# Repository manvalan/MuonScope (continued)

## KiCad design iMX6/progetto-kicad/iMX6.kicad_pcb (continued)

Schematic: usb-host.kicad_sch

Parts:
C212: 1uF; C_0603_1608Metric
C213: 47uF/10V; C_1206_3216Metric
C214: 100nF; C_0603_1608Metric
J9: TYPE-C-31-M-12; USB-C_SMD-TYPE-C-31-M-12_1; MPN TYPE-C-31-M-12; LCSC C165948
J10: Console UART1; PinHeader_1x03_P2.54mm_Vertical; MPN 2.54-1*3P; LCSC C49257
R217, R218: 56k; R_0603_1608Metric
R219: 26.1k 1%; R_0603_1608Metric
R220: 100k; R_0603_1608Metric
R221: 10k; R_0603_1608Metric
U16: TPS2553DBVR; TPS2553DBVR_SOT-23-6_L2.9-W1.6-P0.95-LS2.8-BR; MPN TPS2553DBVR; LCSC C55266
U17: USBLC6-2SC6; SOT-23-6; MPN USBLC6-2SC6; LCSC C7519

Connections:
5V: C212.1, R217.1, R218.1, U16.1 (IN); also elsewhere on the board
/USB host e console/USB2_CC1: J9.A5 (CC1), R217.2
/USB host e console/USB2_CC2: J9.B5 (CC2), R218.2
/USB host e console/USB2_ILIM: R219.1, U16.5 (ILIM)
/USB host e console/VBUS2: C213.1, C214.1, J9.A4B9 (VBUS), J9.B4A9 (VBUS), U16.6 (OUT), U17.5 (VBUS)
DCDC_3V3: R221.1; also elsewhere on the board
GND: C212.2, C213.2, C214.2, J9.1 (EH), J9.2 (EH), J9.3 (EH), J9.4 (EH), J9.A1B12 (GND), J9.B1A12 (GND), J10.3, R219.2, R220.2, U16.2 (GND), U17.2 (GND); also elsewhere on the board
UART1_RX: J10.2; also elsewhere on the board
UART1_TX: J10.1; also elsewhere on the board
USB2_DM: J9.A7 (DN1), J9.B7 (DN2), U17.3 (I/O2), U17.4 (I/O2); also elsewhere on the board
USB2_DP: J9.A6 (DP1), J9.B6 (DP2), U17.1 (I/O1), U17.6 (I/O1); also elsewhere on the board
USB2_OC_N: R221.2, U16.4 (/FAULT); also elsewhere on the board
USB2_VBUS_EN: R220.1, U16.3 (EN); also elsewhere on the board

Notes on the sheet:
USB-C 2 host su USB_OTG2 (ex hub), affiancata alla USB-C 1. VBUS dal TPS2553 (~1 A, RILIM 26.1k), EN su GPIO1_IO04 con 100k a GND, FAULT su SNVS_TAMPER6 con 10k. Rp 56k su CC (sorgente default).
Console Linux su UART1 (al posto del CP2102N di nanoberry): header 1x3 TX, RX, GND a 3.3 V.
USB-C 2 host

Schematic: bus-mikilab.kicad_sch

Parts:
C215: 100nF; C_0603_1608Metric
J11: BUS_POWER_MIKILAB; FPC-SMD_FH12-30S-0.5SH-55; MPN FH12-30S-0.5SH; LCSC C506793
J12: BUS_MIKILAB_MAIN; FPC-SMD_28P-P0.50_FPC-05F-28PH20; MPN FPC-05F-28PH20; LCSC C2856807
R222, R223: 33R; R_0603_1608Metric
R224: 10k; R_0603_1608Metric
R225: 100k; R_0603_1608Metric
R226, R227: 4.7k; R_0603_1608Metric
R228, R229: 2.2k; R_0603_1608Metric
U18, U19, U20, U21, U22, U23: TPD4E05U06DQAR; USON-10_2.5x1.0mm_P0.5mm; MPN TPD4E05U06DQAR

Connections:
/Bus MIKILAB/BUS_1V25_REF: J11.6, J12.6
/Bus MIKILAB/BUS_2V5_REF: J11.5, J12.5
/Bus MIKILAB/BUS_3V3: J11.9, J11.29, J12.3
/Bus MIKILAB/BUS_5V: J11.8, J12.2
/Bus MIKILAB/BUS_VBIAS_1: J11.2, J12.8
/Bus MIKILAB/BUS_VBIAS_2: J11.3, J12.9
/Bus MIKILAB/GND_A: J11.1, J11.4, J11.7, J12.7
/Bus MIKILAB/MAIN_SPI_SCLK: J12.11, R223.2, U20.2 (D1-)
/Bus MIKILAB/PWR_SPI_SCLK: J11.11, R222.2, U18.1 (D1+)
DAC61402_FAULT: J11.20, U20.1 (D1+); also elsewhere on the board
DCDC_3V3: R226.1, R227.1, R228.1, R229.1; also elsewhere on the board
GND: C215.2, J11.10, J11.14, J11.21, J11.22, J11.23, J11.27, J11.28, J11.30, J11.31, J11.32, J12.1, J12.4, J12.10, J12.16, J12.25, J12.26, J12.27, J12.29, J12.30, R224.2, R225.2, U18.3 (GND), U18.8 (GND), U19.3 (GND), U19.8 (GND), U20.3 (GND), U20.8 (GND), U21.3 (GND), U21.8 (GND), U22.3 (GND), U22.8 (GND), U23.3 (GND), U23.8 (GND); also elsewhere on the board
MAIN_HIT_N: J12.28, R227.2, U23.4 (D2+); also elsewhere on the board
MAIN_I2C_SCL: J12.15, R228.2, U21.2 (D1-); also elsewhere on the board
MAIN_I2C_SDA: J12.14, R229.2, U21.1 (D1+); also elsewhere on the board
MAIN_SPI_ADDR_0: J12.18, U21.5 (D2-); also elsewhere on the board
MAIN_SPI_ADDR_1: J12.19, U22.1 (D1+); also elsewhere on the board
MAIN_SPI_ADDR_2: J12.20, U22.2 (D1-); also elsewhere on the board
MAIN_SPI_ALERT_N: J12.24, R226.2, U23.2 (D1-); also elsewhere on the board
MAIN_SPI_CS_MASTER: J12.17, U21.4 (D2+); also elsewhere on the board
MAIN_SPI_MISO: J12.13, U20.5 (D2-); also elsewhere on the board
MAIN_SPI_MOSI: J12.12, U20.4 (D2+); also elsewhere on the board
MAIN_SPI_PREFIX_0: J12.21, U22.4 (D2+); also elsewhere on the board
MAIN_SPI_PREFIX_1: J12.22, U22.5 (D2-); also elsewhere on the board
MAIN_SPI_PREFIX_2: J12.23, U23.1 (D1+); also elsewhere on the board
MAIN_SPI_SCLK_S: R223.1; also elsewhere on the board
PWR_SPI_DAC_CS: J11.17, U19.2 (D1-); also elsewhere on the board
PWR_SPI_INA239A_CS: J11.15, U18.5 (D2-); also elsewhere on the board
PWR_SPI_INA239B_CS: J11.16, U19.1 (D1+); also elsewhere on the board
PWR_SPI_MISO: J11.13, U18.4 (D2+); also elsewhere on the board
PWR_SPI_MOSI: J11.12, U18.2 (D1-); also elsewhere on the board
PWR_SPI_SCLK_S: R222.1; also elsewhere on the board
VBIAS_ENABLE: J11.19, R225.1, U19.5 (D2-); also elsewhere on the board
VIN_SYS: C215.1, J11.24, J11.25, J11.26; also elsewhere on the board
VREF_ENABLE: J11.18, R224.1, U19.4 (D2+); also elsewhere on the board

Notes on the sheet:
J BUS_POWER 30 pin (Hirose FH12-30S) su ECSPI4 (pad ENET2, ex touch), J MAIN 28 pin REV5.1 (XUNPU FPC-05F-28PH20) su ECSPI1 (pad CSI_DATA04-07, ex espansione P1). Mappa dei connettori come SchedaIMX6ULL-SD.
Serie 33R sui clock SPI. Pull-up 4.7k su ALERT#/HIT#, 2.2k su I2C. VREF_ENABLE 10k e VBIAS_ENABLE 100k a GND. CS e FAULT con i pull-up interni del 6ULL. ESD TPD4E05U06DQA sulle linee logiche.
Serie SPI 33R, solo clock
Livelli di riposo
Disaccoppiamento

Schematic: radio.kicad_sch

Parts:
C216, C217: DNP; C_0603_1608Metric; not fitted
C218: 22uF/10V; C_0805_2012Metric
C219: 100nF; C_0603_1608Metric
C220: 1uF; C_0603_1608Metric
J13: U.FL; U.FL_Hirose_U.FL-R-SMT-1_Vertical
R230: 22R; R_0603_1608Metric
R231, R232: 10k; R_0603_1608Metric
R233: 0R; R_0603_1608Metric
U24: BL-M8723DS1; LB-LINK_BL-M8723DS1_LGA-44_12x12mm; MPN BL-M8723DS1
U25: AP2112K-3.3TRG1; SOT95P285X140-5N; MPN AP2112K-3.3TRG1; LCSC C51118

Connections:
5V: C220.1, U25.1 (VIN), U25.3 (EN); also elsewhere on the board
/Radio/3V3_WIFI: C218.1, C219.1, U24.9 (VDD33), U24.22 (VDIO), U25.5 (VOUT)
/Radio/SD2_CLK: R230.2, U24.17 (SD_CLK)
/Radio/WL_ANT: C216.1, R233.1, U24.2 (ANT)
/Radio/WL_ANT_C: C217.1, J13.1 (In), R233.2
BT_DIS_N: R232.1, U24.34 (BT_DIS_N); also elsewhere on the board
BT_HOST_WAKE: U24.6 (BT_HOST_WAKE); also elsewhere on the board
BT_UART_CTS: U24.44 (UART_CTS); also elsewhere on the board
BT_UART_RX: U24.43 (UART_RX); also elsewhere on the board
BT_UART_TX: U24.42 (UART_TX); also elsewhere on the board
GND: C216.2, C217.2, C218.2, C219.2, C220.2, J13.2 (Ext), R231.2, R232.2, U24.1 (GND), U24.3 (GND), U24.20 (GND), U24.31 (GND), U24.33 (GND), U24.36 (GND), U24.41 (GND), U25.2 (GND); also elsewhere on the board
SD2_CLK_S: R230.1; also elsewhere on the board
SD2_CMD: U24.16 (SD_CMD); also elsewhere on the board
SD2_D0: U24.18 (SD_D0); also elsewhere on the board
SD2_D1: U24.19 (SD_D1); also elsewhere on the board
SD2_D2: U24.14 (SD_D2); also elsewhere on the board
SD2_D3: U24.15 (SD_D3); also elsewhere on the board
WL_DIS_N: R231.1, U24.12 (WL_DIS_N); also elsewhere on the board
WL_WAKE_HOST: U24.13 (WL_WAKE_HOST); also elsewhere on the board

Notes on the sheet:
BL-M8723DS1 (RTL8723DS) su uSDHC2 sui pad CSI (VSYNC = CLK, HSYNC = CMD, DATA00-03), libero perche' il boot e' da QSPI; BT su UART2 (TX, RX, RTS -> CTS del modulo). SDIO con i pull-up interni del 6ULL.
Alimentazione 3.3 V dedicata (AP2112K da 5V). WL_DIS# e BT_DIS# con 10k a GND. Antenna su U.FL con rete pi 0R + 2 DNP. Footprint LGA-44 dal datasheet LB-LINK V1.0.1.3.
Wi-Fi: 22R su CLK, enable a GND, rete pi

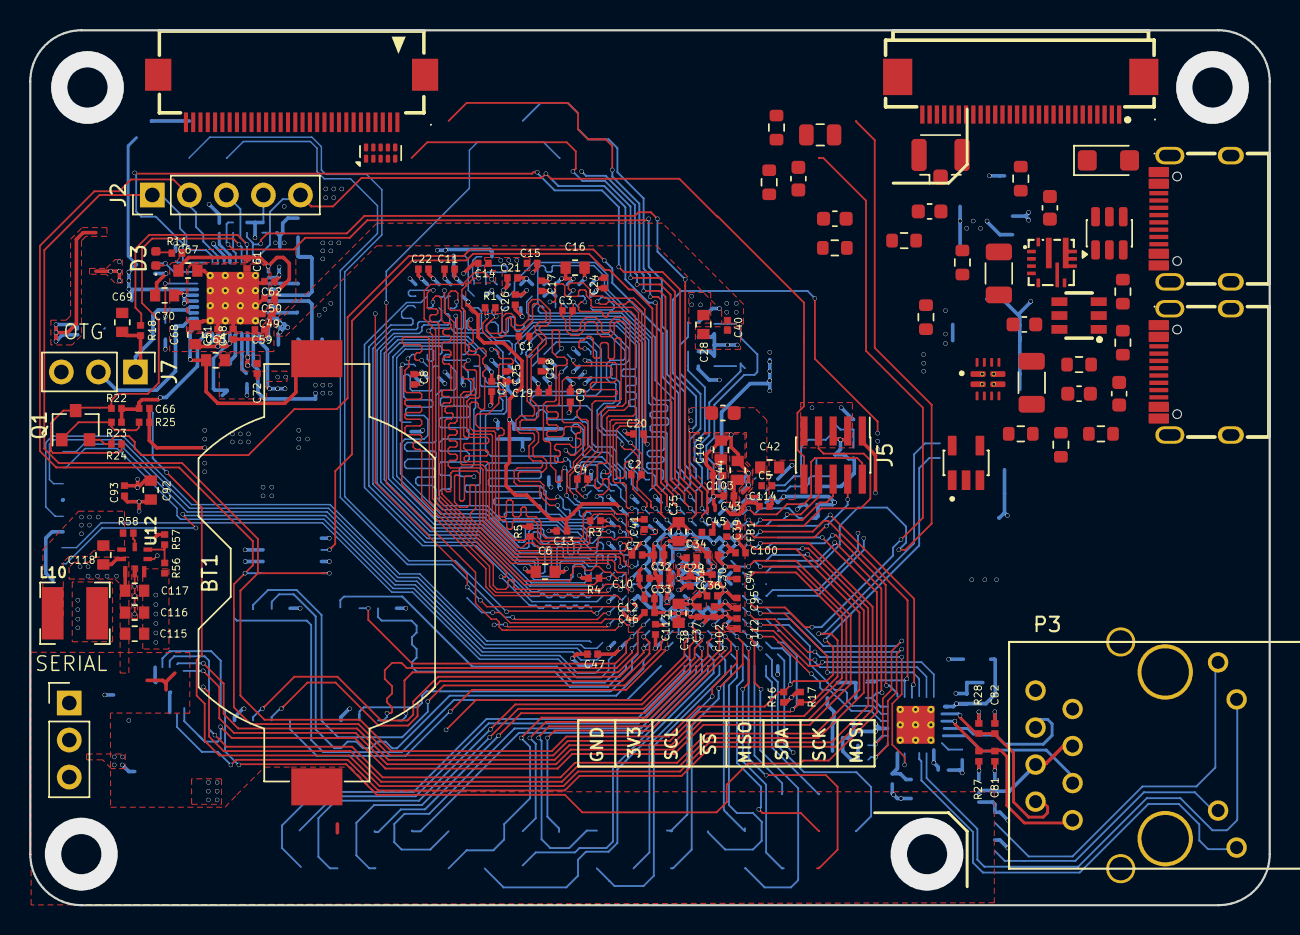
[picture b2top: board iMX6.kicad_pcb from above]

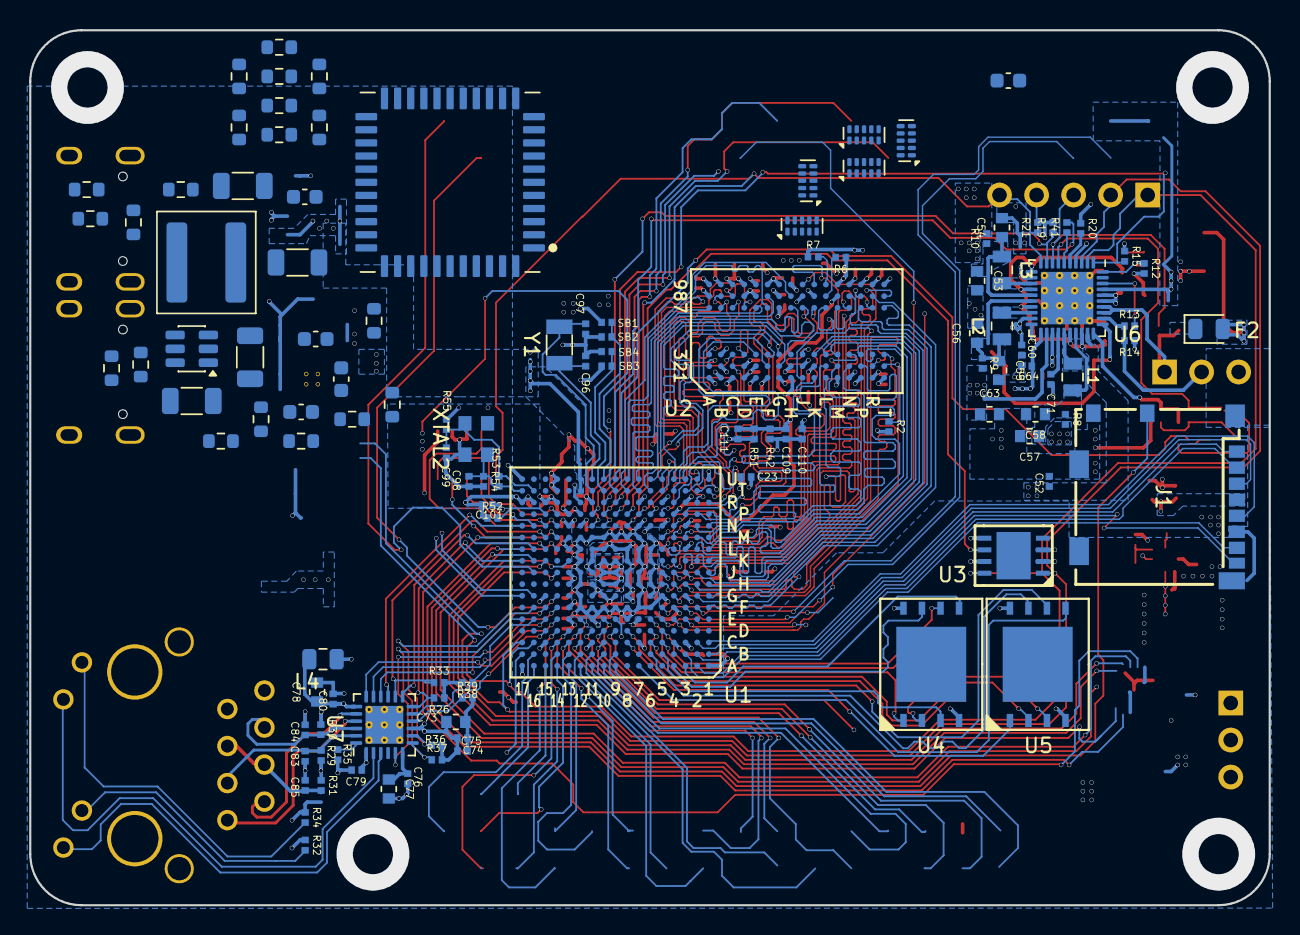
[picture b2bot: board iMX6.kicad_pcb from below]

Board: 4 copper layers, 85.0 x 60.0 mm, 260 parts (119 on the bottom side), 238 nets.

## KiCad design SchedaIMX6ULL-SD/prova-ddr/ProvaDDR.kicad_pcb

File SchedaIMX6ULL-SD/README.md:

# Scheda i.MX 6ULL con sola microSD (MuonScope)

Variante di `../SchedaIMX6ULL/` senza SSD: niente M.2, bridge JMS578, buck dell'SSD, hub FE1.1s e pila di backup. BOM in `bom/bom-imx6ull-sd.csv`.

- SoC NXP i.MX 6ULL (MCIMX6Y2CVM08AB), DDR3L 1 GB
- **Boot da NOR QSPI 16 MB** (W25Q128JV, SS0), **rootfs UBIFS su SPI NAND SLC 512 MB** (W25N04KV, SS1), microSD per dati o boot alternativo
- USB-C 1 device/download seriale e alimentazione, USB-C 2 host diretta su USB_OTG2
- Ethernet 10/100, Wi-Fi/BT SDIO, GNSS NEO-M9N con PPS ed EXTINT su GPT1, bus MIKILAB

La NAND è la W25N04KVZEIR. Ripieghi sulla stessa impronta WSON-8 8x6, se serve meno capacità o la 512 MB non si trova: W25N02KV (256 MB) e W25N01GV (128 MB), entrambe a 3.3 V. Non W25N04KW o W25N04LW, che sono a 1.8 V.

| Percorso | Cosa |
|---|---|
| `progetto-kicad/` | Progetto KiCad 10 `SchedaIMX6ULL-SD.kicad_pro` |
| `schema-imx6ull-sd.pdf` | Schema gerarchico completo |
| `pcb-placement-imx6ull-sd.pdf` / `.png` | Placement, top e bottom |
| `docs/scelte-progetto.md` | Differenze dalla versione SSD, **punti da verificare** |
| `docs/pcb-placement.md` | Scheda, stackup, regole, stima di fanout, esito DRC |
| `docs/pinmap-imx6ull.md` | Mappa sfera per sfera con la net |
| `generatori/` | `build.sh` rifà lo schema, `build_pcb.sh` il PCB, `fanout.py` la stima di fanout |

```bash
sh SchedaIMX6ULL-SD/generatori/build.sh
sh SchedaIMX6ULL-SD/generatori/build_pcb.sh
```

## Stato

- Schema gerarchico, **ERC 0 violazioni**.
- PCB **80 x 100 mm, 4 strati**, solo placement, decoupling sul bottom sotto SoC e DDR3L, **DRC 0 violazioni, parità schema/PCB 0 problemi**. 229 componenti, di cui 176 passivi.
- **Non sbrogliato**: il fanout a 4 strati è solo stimato, con margine piccolo.

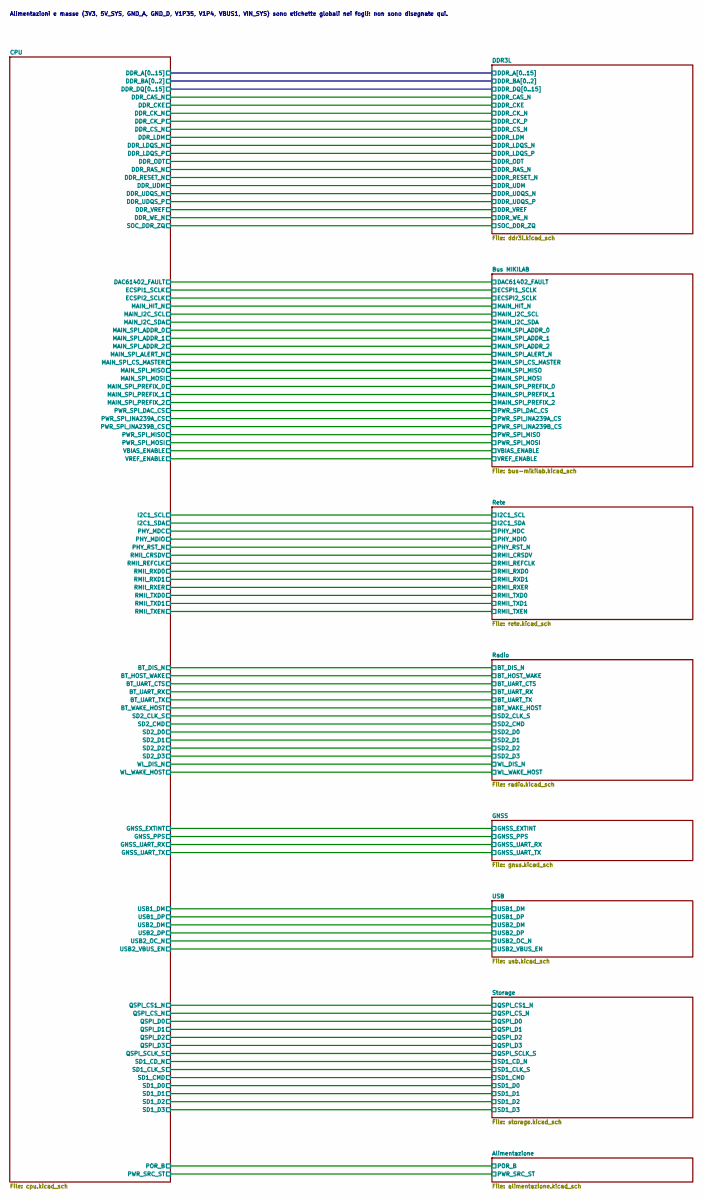
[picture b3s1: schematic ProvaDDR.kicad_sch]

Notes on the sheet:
Alimentazioni e masse (3V3, 5V_SYS, GND_A, GND_D, V1P35, V1P4, VBUS1, VIN_SYS) sono etichette globali nei fogli: non sono disegnate qui.

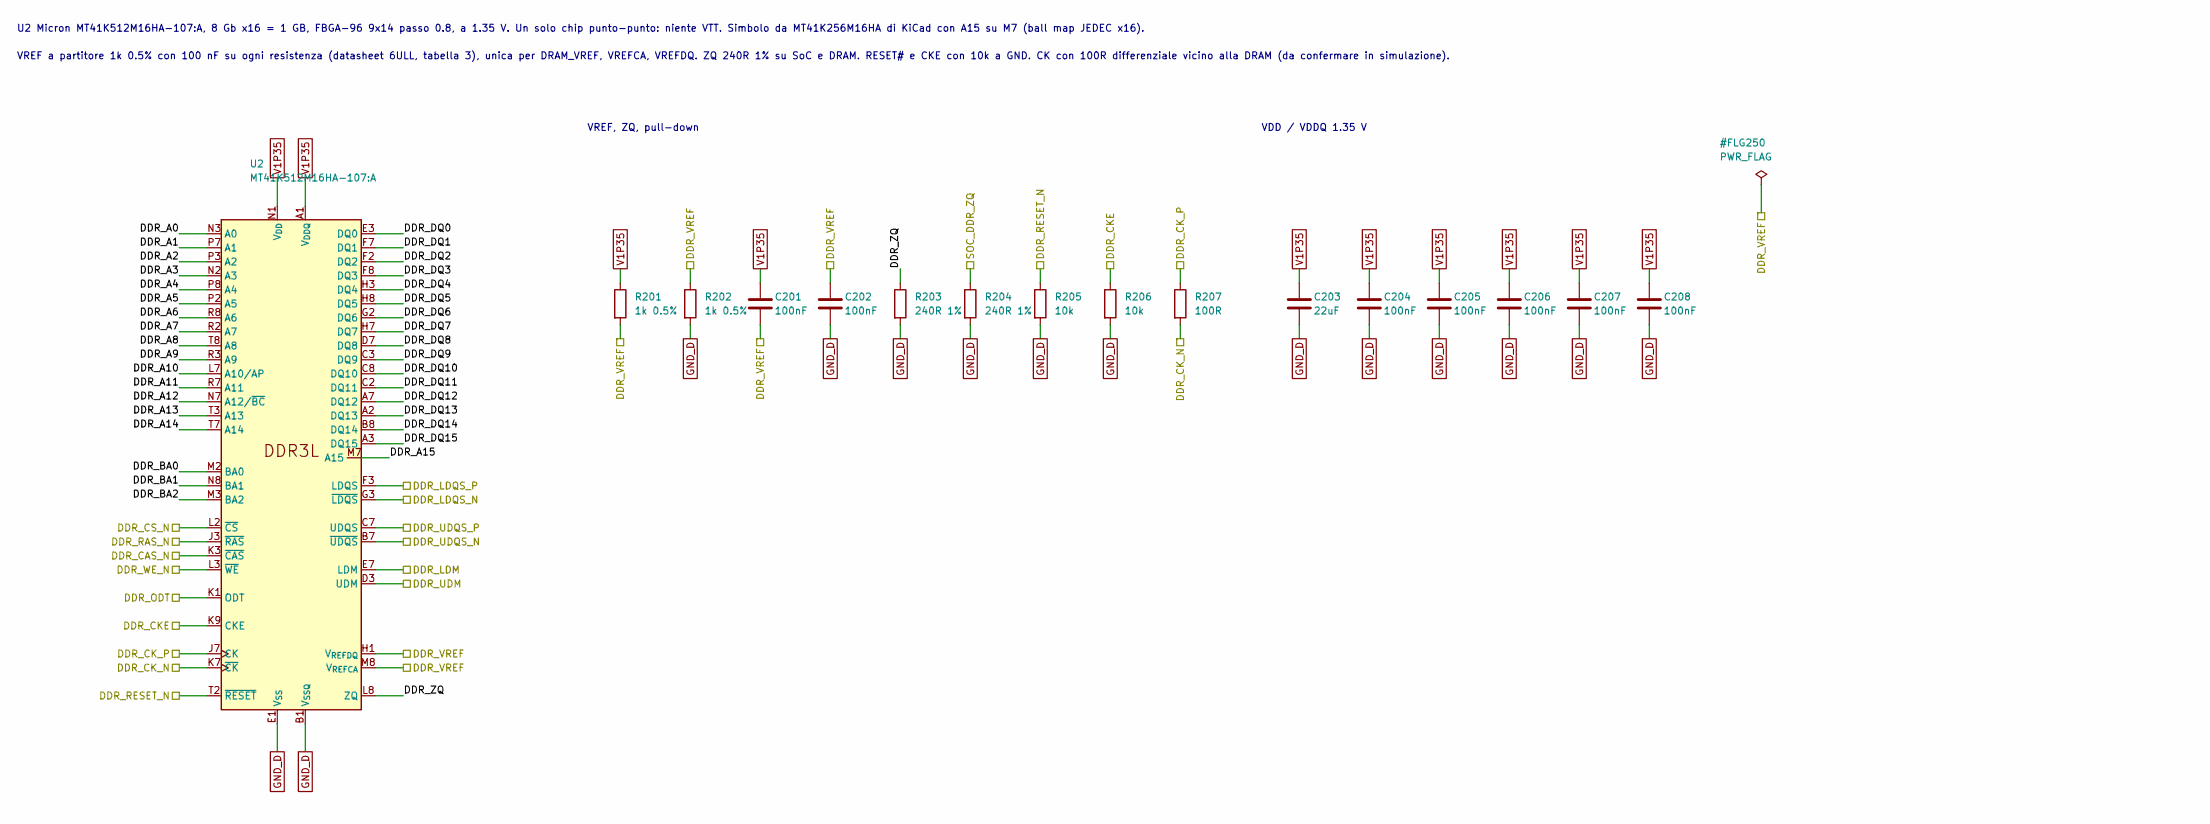
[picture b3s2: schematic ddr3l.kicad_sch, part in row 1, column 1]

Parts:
C201, C202, C204, C205, C206, C207, C208: 100nF; C_0603_1608Metric
C203: 22uF; C_0805_2012Metric
R201, R202: 1k 0.5%; R_0603_1608Metric
R203, R204: 240R 1%; R_0603_1608Metric
R205, R206: 10k; R_0603_1608Metric
R207: 100R; R_0603_1608Metric
U2: MT41K512M16HA-107:A; Micron_FBGA-96_9x14mm_Layout9x16_P0.8mm; MPN MT41K512M16HA-107:A

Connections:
/CPU/DDR_A0: U2.N3 (A0); also elsewhere on the board
/CPU/DDR_A1: U2.P7 (A1); also elsewhere on the board
/CPU/DDR_A2: U2.P3 (A2); also elsewhere on the board
/CPU/DDR_A3: U2.N2 (A3); also elsewhere on the board
/CPU/DDR_A4: U2.P8 (A4); also elsewhere on the board
/CPU/DDR_A5: U2.P2 (A5); also elsewhere on the board
/CPU/DDR_A6: U2.R8 (A6); also elsewhere on the board
/CPU/DDR_A7: U2.R2 (A7); also elsewhere on the board
/CPU/DDR_A8: U2.T8 (A8); also elsewhere on the board
/CPU/DDR_A9: U2.R3 (A9); also elsewhere on the board
/CPU/DDR_A10: U2.L7 (A10/AP); also elsewhere on the board
/CPU/DDR_A11: U2.R7 (A11); also elsewhere on the board
/CPU/DDR_A12: U2.N7 (A12/~BC); also elsewhere on the board
/CPU/DDR_A13: U2.T3 (A13); also elsewhere on the board
/CPU/DDR_A14: U2.T7 (A14); also elsewhere on the board
/CPU/DDR_A15: U2.M7 (A15); also elsewhere on the board
/CPU/DDR_BA0: U2.M2 (BA0); also elsewhere on the board
/CPU/DDR_BA1: U2.N8 (BA1); also elsewhere on the board
/CPU/DDR_BA2: U2.M3 (BA2); also elsewhere on the board
/CPU/DDR_CAS_N: U2.K3 (~CAS); also elsewhere on the board
/CPU/DDR_CKE: R206.1, U2.K9 (CKE); also elsewhere on the board
/CPU/DDR_CK_N: R207.2, U2.K7 (~CK); also elsewhere on the board
/CPU/DDR_CK_P: R207.1, U2.J7 (CK); also elsewhere on the board
/CPU/DDR_CS_N: U2.L2 (~CS); also elsewhere on the board
/CPU/DDR_DQ0: U2.E3 (DQ0); also elsewhere on the board
/CPU/DDR_DQ1: U2.F7 (DQ1); also elsewhere on the board
/CPU/DDR_DQ2: U2.F2 (DQ2); also elsewhere on the board
/CPU/DDR_DQ3: U2.F8 (DQ3); also elsewhere on the board
/CPU/DDR_DQ4: U2.H3 (DQ4); also elsewhere on the board
/CPU/DDR_DQ5: U2.H8 (DQ5); also elsewhere on the board
/CPU/DDR_DQ6: U2.G2 (DQ6); also elsewhere on the board
/CPU/DDR_DQ7: U2.H7 (DQ7); also elsewhere on the board
/CPU/DDR_DQ8: U2.D7 (DQ8); also elsewhere on the board
/CPU/DDR_DQ9: U2.C3 (DQ9); also elsewhere on the board
/CPU/DDR_DQ10: U2.C8 (DQ10); also elsewhere on the board
/CPU/DDR_DQ11: U2.C2 (DQ11); also elsewhere on the board
/CPU/DDR_DQ12: U2.A7 (DQ12); also elsewhere on the board
/CPU/DDR_DQ13: U2.A2 (DQ13); also elsewhere on the board
/CPU/DDR_DQ14: U2.B8 (DQ14); also elsewhere on the board
/CPU/DDR_DQ15: U2.A3 (DQ15); also elsewhere on the board
/CPU/DDR_LDM: U2.E7 (LDM); also elsewhere on the board
/CPU/DDR_LDQS_N: U2.G3 (~LDQS); also elsewhere on the board
/CPU/DDR_LDQS_P: U2.F3 (LDQS); also elsewhere on the board
/CPU/DDR_ODT: U2.K1 (ODT); also elsewhere on the board
/CPU/DDR_RAS_N: U2.J3 (~RAS); also elsewhere on the board
/CPU/DDR_RESET_N: R205.1, U2.T2 (~RESET); also elsewhere on the board
/CPU/DDR_UDM: U2.D3 (UDM); also elsewhere on the board
/CPU/DDR_UDQS_N: U2.B7 (~UDQS); also elsewhere on the board
/CPU/DDR_UDQS_P: U2.C7 (UDQS); also elsewhere on the board
/CPU/DDR_VREF: C201.2, C202.1, R201.2, R202.1, U2.H1 (V_{REFDQ}), U2.M8 (V_{REFCA}); also elsewhere on the board
/CPU/DDR_WE_N: U2.L3 (~WE); also elsewhere on the board
/CPU/SOC_DDR_ZQ: R204.1; also elsewhere on the board
/DDR3L/DDR_ZQ: R203.1, U2.L8 (ZQ)
GND_D: C202.2, C203.2, C204.2, C205.2, C206.2, C207.2, C208.2, R202.2, R203.2, R204.2, R205.2, R206.2, U2.A9 (V_{SS}), U2.B1 (V_{SSQ}), U2.B3 (V_{SS}), U2.B9 (V_{SSQ}), U2.D1 (V_{SSQ}), U2.D8 (V_{SSQ}), U2.E1 (V_{SS}), U2.E2 (V_{SSQ}), U2.E8 (V_{SSQ}), U2.F9 (V_{SSQ}), U2.G1 (V_{SSQ}), U2.G8 (V_{SS}), U2.G9 (V_{SSQ}), U2.J2 (V_{SS}), U2.J8 (V_{SS}), U2.M1 (V_{SS}), U2.M9 (V_{SS}), U2.P1 (V_{SS}), U2.P9 (V_{SS}), U2.T1 (V_{SS}), U2.T9 (V_{SS}); also elsewhere on the board
V1P35: C201.1, C203.1, C204.1, C205.1, C206.1, C207.1, C208.1, R201.1, U2.A1 (V_{DDQ}), U2.A8 (V_{DDQ}), U2.B2 (V_{DD}), U2.C1 (V_{DDQ}), U2.C9 (V_{DDQ}), U2.D2 (V_{DDQ}), U2.D9 (V_{DD}), U2.E9 (V_{DDQ}), U2.F1 (V_{DDQ}), U2.G7 (V_{DD}), U2.H2 (V_{DDQ}), U2.H9 (V_{DDQ}), U2.K2 (V_{DD}), U2.K8 (V_{DD}), U2.N1 (V_{DD}), U2.N9 (V_{DD}), U2.R1 (V_{DD}), U2.R9 (V_{DD}); also elsewhere on the board

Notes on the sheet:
U2 Micron MT41K512M16HA-107:A, 8 Gb x16 = 1 GB, FBGA-96 9x14 passo 0.8, a 1.35 V. Un solo chip punto-punto: niente VTT. Simbolo da MT41K256M16HA di KiCad con A15 su M7 (ball map JEDEC x16).
VREF a partitore 1k 0.5% con 100 nF su ogni resistenza (datasheet 6ULL, tabella 3), unica per DRAM_VREF, VREFCA, VREFDQ. ZQ 240R 1% su SoC e DRAM. RESET# e CKE con 10k a GND. CK con 100R differenziale vicino alla DRAM (da confermare in simulazione).
VREF, ZQ, pull-down
VDD / VDDQ 1.35 V

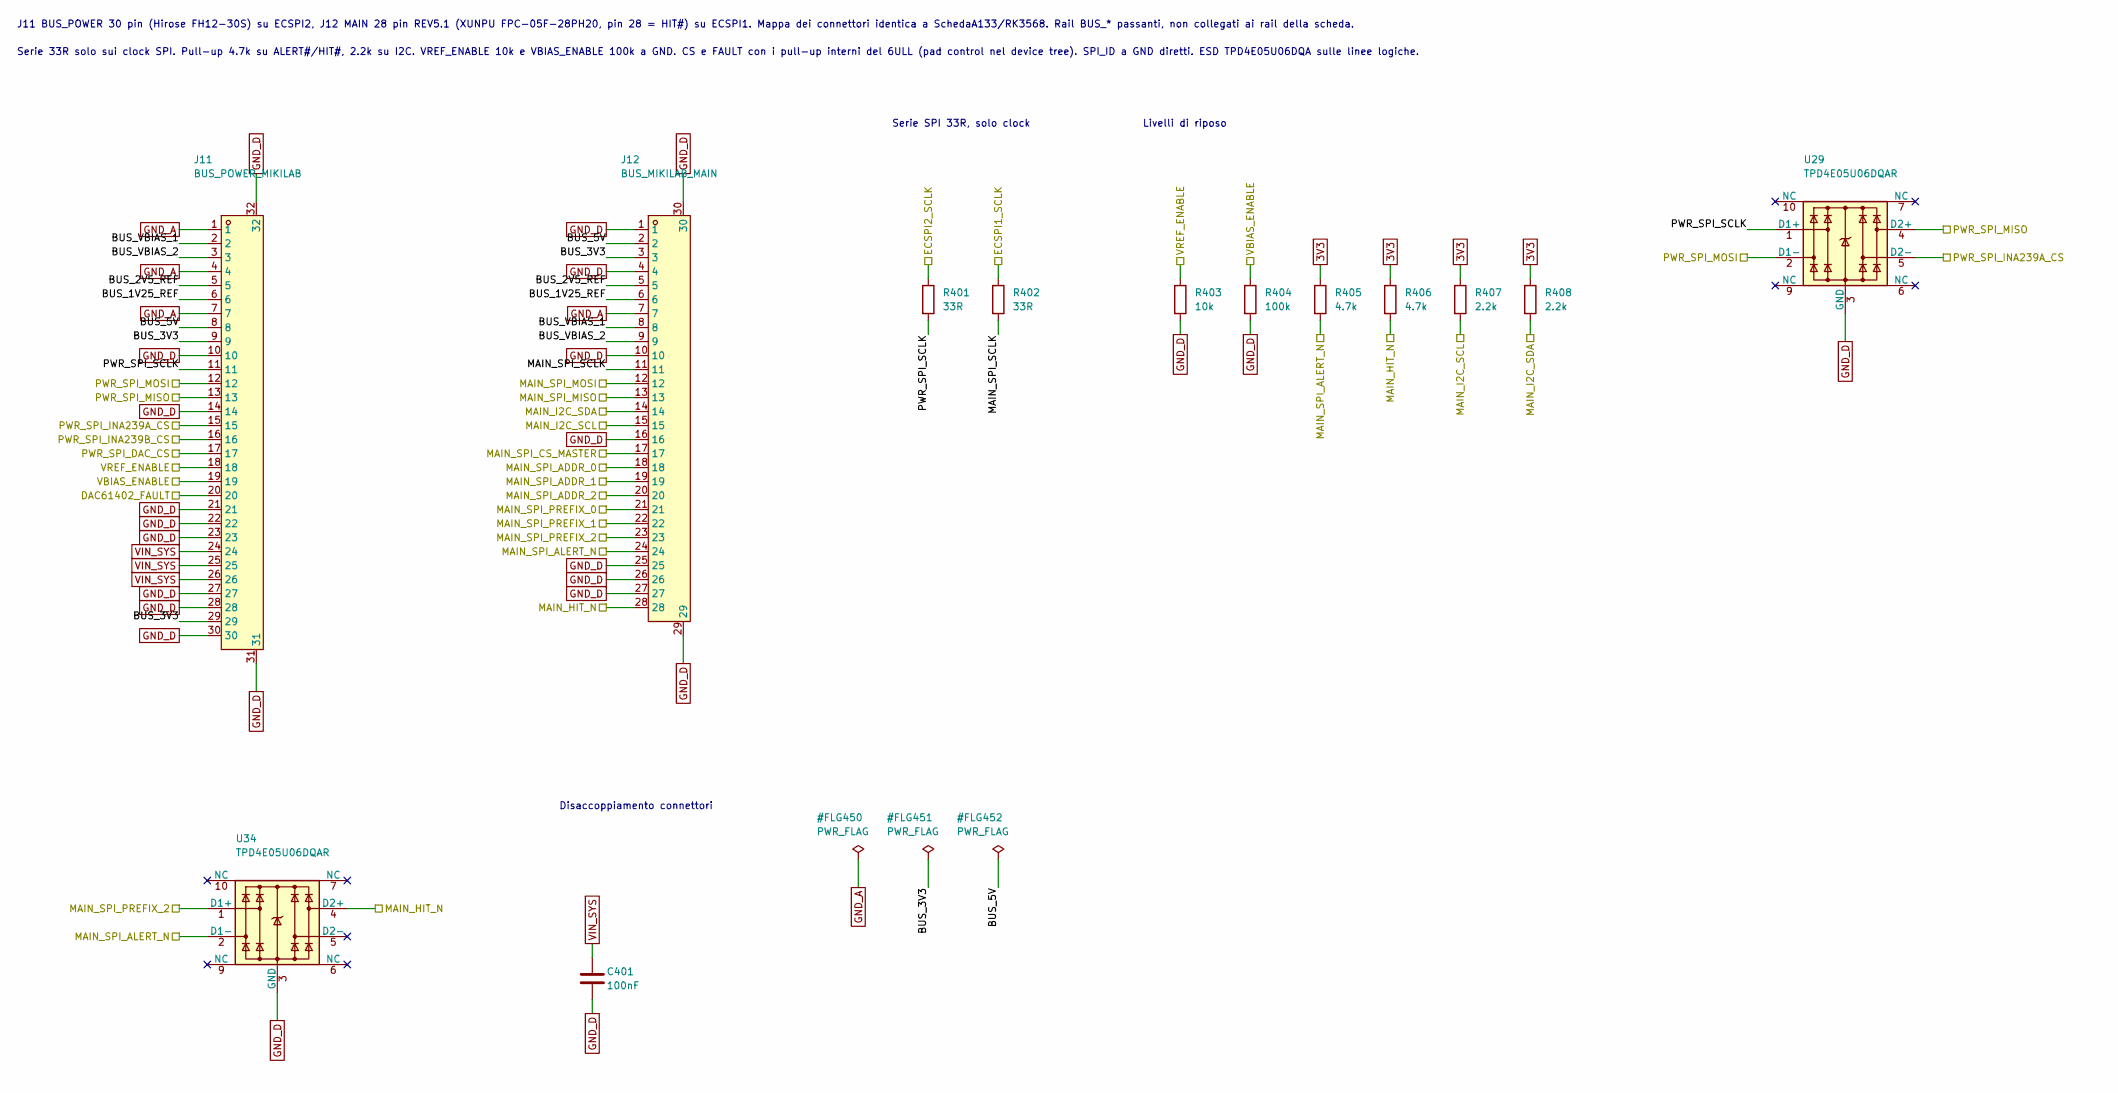
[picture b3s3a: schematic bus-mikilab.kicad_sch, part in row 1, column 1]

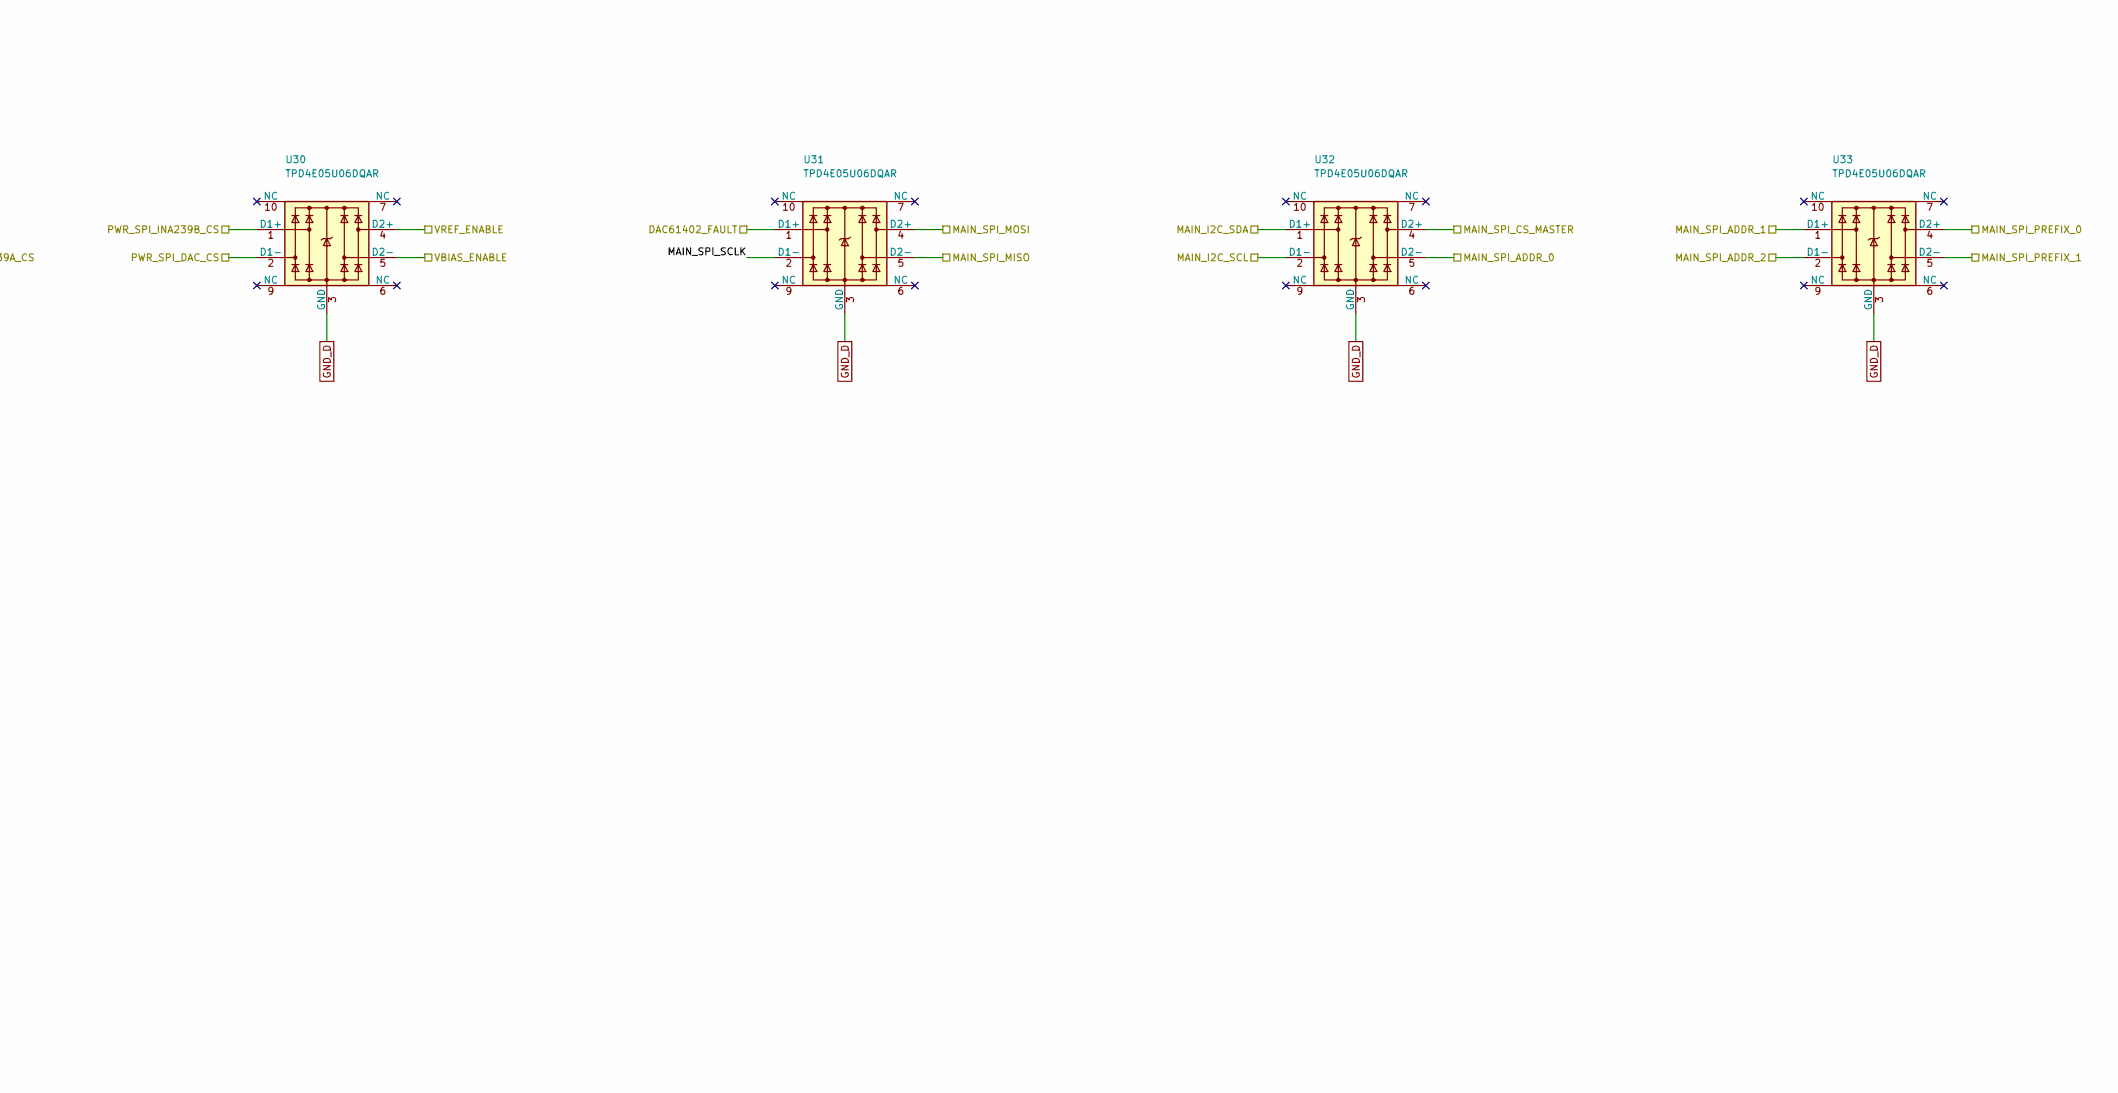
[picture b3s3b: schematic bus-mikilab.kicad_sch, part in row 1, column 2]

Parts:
C401: 100nF; C_0603_1608Metric
J11: BUS_POWER_MIKILAB; FPC-SMD_FH12-30S-0.5SH-55; MPN FH12-30S-0.5SH; LCSC C506793
J12: BUS_MIKILAB_MAIN; FPC-SMD_28P-P0.50_FPC-05F-28PH20; MPN FPC-05F-28PH20; LCSC C2856807
R401, R402: 33R; R_0603_1608Metric
R403: 10k; R_0603_1608Metric
R404: 100k; R_0603_1608Metric
R405, R406: 4.7k; R_0603_1608Metric
R407, R408: 2.2k; R_0603_1608Metric
U29, U30, U31, U32, U33, U34: TPD4E05U06DQAR; USON-10_2.5x1.0mm_P0.5mm; MPN TPD4E05U06DQAR

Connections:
3V3: R405.1, R406.1, R407.1, R408.1; also elsewhere on the board
/Bus MIKILAB/BUS_1V25_REF: J11.6, J12.6
/Bus MIKILAB/BUS_2V5_REF: J11.5, J12.5
/Bus MIKILAB/BUS_3V3: J11.9, J11.29, J12.3
/Bus MIKILAB/BUS_5V: J11.8, J12.2
/Bus MIKILAB/BUS_VBIAS_1: J11.2, J12.8
/Bus MIKILAB/BUS_VBIAS_2: J11.3, J12.9
/Bus MIKILAB/DAC61402_FAULT: J11.20, U31.1 (D1+); also elsewhere on the board
/Bus MIKILAB/ECSPI1_SCLK: R402.1; also elsewhere on the board
/Bus MIKILAB/ECSPI2_SCLK: R401.1; also elsewhere on the board
/Bus MIKILAB/MAIN_HIT_N: J12.28, R406.2, U34.4 (D2+); also elsewhere on the board
/Bus MIKILAB/MAIN_I2C_SCL: J12.15, R407.2, U32.2 (D1-); also elsewhere on the board
/Bus MIKILAB/MAIN_I2C_SDA: J12.14, R408.2, U32.1 (D1+); also elsewhere on the board
/Bus MIKILAB/MAIN_SPI_ADDR_0: J12.18, U32.5 (D2-); also elsewhere on the board
/Bus MIKILAB/MAIN_SPI_ADDR_1: J12.19, U33.1 (D1+); also elsewhere on the board
/Bus MIKILAB/MAIN_SPI_ADDR_2: J12.20, U33.2 (D1-); also elsewhere on the board
/Bus MIKILAB/MAIN_SPI_ALERT_N: J12.24, R405.2, U34.2 (D1-); also elsewhere on the board
/Bus MIKILAB/MAIN_SPI_CS_MASTER: J12.17, U32.4 (D2+); also elsewhere on the board
/Bus MIKILAB/MAIN_SPI_MISO: J12.13, U31.5 (D2-); also elsewhere on the board
/Bus MIKILAB/MAIN_SPI_MOSI: J12.12, U31.4 (D2+); also elsewhere on the board
/Bus MIKILAB/MAIN_SPI_PREFIX_0: J12.21, U33.4 (D2+); also elsewhere on the board
/Bus MIKILAB/MAIN_SPI_PREFIX_1: J12.22, U33.5 (D2-); also elsewhere on the board
/Bus MIKILAB/MAIN_SPI_PREFIX_2: J12.23, U34.1 (D1+); also elsewhere on the board
/Bus MIKILAB/MAIN_SPI_SCLK: J12.11, R402.2, U31.2 (D1-)
/Bus MIKILAB/PWR_SPI_DAC_CS: J11.17, U30.2 (D1-); also elsewhere on the board
/Bus MIKILAB/PWR_SPI_INA239A_CS: J11.15, U29.5 (D2-); also elsewhere on the board
/Bus MIKILAB/PWR_SPI_INA239B_CS: J11.16, U30.1 (D1+); also elsewhere on the board
/Bus MIKILAB/PWR_SPI_MISO: J11.13, U29.4 (D2+); also elsewhere on the board
/Bus MIKILAB/PWR_SPI_MOSI: J11.12, U29.2 (D1-); also elsewhere on the board
/Bus MIKILAB/PWR_SPI_SCLK: J11.11, R401.2, U29.1 (D1+)
/Bus MIKILAB/VBIAS_ENABLE: J11.19, R404.1, U30.5 (D2-); also elsewhere on the board
/Bus MIKILAB/VREF_ENABLE: J11.18, R403.1, U30.4 (D2+); also elsewhere on the board
GND_A: J11.1, J11.4, J11.7, J12.7
GND_D: C401.2, J11.10, J11.14, J11.21, J11.22, J11.23, J11.27, J11.28, J11.30, J11.31, J11.32, J12.1, J12.4, J12.10, J12.16, J12.25, J12.26, J12.27, J12.29, J12.30, R403.2, R404.2, U29.3 (GND), U29.8 (GND), U30.3 (GND), U30.8 (GND), U31.3 (GND), U31.8 (GND), U32.3 (GND), U32.8 (GND), U33.3 (GND), U33.8 (GND), U34.3 (GND), U34.8 (GND); also elsewhere on the board
VIN_SYS: C401.1, J11.24, J11.25, J11.26; also elsewhere on the board

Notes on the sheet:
J11 BUS_POWER 30 pin (Hirose FH12-30S) su ECSPI2, J12 MAIN 28 pin REV5.1 (XUNPU FPC-05F-28PH20, pin 28 = HIT#) su ECSPI1. Mappa dei connettori identica a SchedaA133/RK3568. Rail BUS_* passanti, non collegati ai rail della scheda.
Serie 33R solo sui clock SPI. Pull-up 4.7k su ALERT#/HIT#, 2.2k su I2C. VREF_ENABLE 10k e VBIAS_ENABLE 100k a GND. CS e FAULT con i pull-up interni del 6ULL (pad control nel device tree). SPI_ID a GND diretti. ESD TPD4E05U06DQA sulle linee logiche.
Serie SPI 33R, solo clock
Livelli di riposo
Disaccoppiamento connettori
